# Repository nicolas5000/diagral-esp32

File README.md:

# diagral-uart-esp32
This project permits to connect to Diagral alarm system DIAG91AGFK using the 20 pins connector on the back (the connector used for the GSM board DIAG55AAX).

It permits to get status from and modify state of the alarm system as it could be done using call and SMS with official DIAG55AAX from Diagral, but using local MQTT connection... and it is directly recognized by Home Assistant!

This project is originally tested on XIAO-ESP32-S3 (with battery management by ESP32 board) and Waveshare ESP32-C6 (with battery management by the Diagral alarm system) hardware and based on ESP-IDF SDK version 6.0.2. It should also work with any other board compatible with Waveshare ESP32-S3 and ESP32-C6 board pinout.

This project is open source: you can reuse it and modify it, but please add a link to my project.
If you like this project you can [contribute](#how-to-contribute) or [buy me a coffee](https://buymeacoffee.com/nicolas5000) to support the tens of hours I spent on it :blush:.

### Why I did this project

From Diagral, DIAG55AAX (also known as DIAG55AAX1) is a 2G only mobile network board and DIAG55AAX5 is 2G/3G mobile network board. These boards will not work anymore in the future as the 2G and 3G mobile networks are being replaced by 4G and 5G networks. Of course you can buy the official Diagral 4G device to replace your old DIAG55AAX module.

The goal of this project is to connect your Diagral system locally to your Home Assistant without any Cloud based solution.

### **Disclaimer**  
> [!CAUTION]
> This tool is designed for educational and testing purposes, provided "as is", without warranty of any kind. It has no link with Diagral company. Creators and contributors are not responsible for any misuse or damage caused by this tool. Keep in mind that you should have a secure MQTT and Home Assistant instances to avoid any attack on your alarm system from your domotics.

### **Security**
To use this project in a secure way, you shall:
- Put the board on the back of the DIAG91AGFK so it is protected by your alarm system tamper mechanism.
- Put a password on command line access (at least in production, when not testing anymore).
- Use a secure network (Wifi password...).
- Use a secure MQTT connection (strong password, certificate...).
- Protect your Home Assistant access.
- If you want the best:
  - Sign your firmware and enable secure boot (see ESP-IDF documentation). This risk can be mitigated by using [HTTPS server for OTA update](#ota-over-https).
  - Enable flash encryption (see ESP-IDF documentation) to protect your Wifi password, command-line password and MQTT password. This risk is mitigated by putting the ESP32 on the back of the DIAG91AGFK (protected by your alarm system tamper mechanism).

### Documentation
This documentation contains useful information about the project, especially:
- [Hardware requirements](README.md#hardware-requirements) to use the project
- [Software configuration](doc/configuration.md) (hardware pins used, network and MQTT settings, ...)
- [Using command line](doc/command_line.md) to test and configure the project
- [MQTT topics and messages](doc/mqtt.md)
- [The project development](doc/development_guide.md) (structure of the project, how the source code is organized if you want to contribute or fork...)
- [The current knowledge about the protocol and commands](doc/protocol.md) used between DIAG91AGFK and DIAG55AAX

### Support
I try to give support on my free time. If you have questions you can open a subject and ask directly in English (for everyone to understand) or in French.

### Project status

These features are currently available:
- Get state from Diagral alarm system:
  - Mode (idle, setup, test)
  - Zones 1 to 4 status (disarmed, arming, armed, armed "home", triggered)
  - Battery charging state. Note: it works only if you have a battery connected to provide power to the device!
- Control the alarm system: Arm/"Arm home"/Disarm with or withour PIN code (choose before building firmware or from command line, can't be modified from MQTT and Home Assistant).
- Events:
  - Error event: event type (tamper, main power, battery, radio link, internet link, arm cancelled reason), harware type (system, sensor, command, siren), hardware number
  - Detection event: event type, sensor type, sensor number
  - Alert event: alert type (fire, alert, silent alert, duress disarm), command number
- Control the ESP32:
  - Reboot
  - Enable/disable logging
  - Enable/disable passive mode
- Connectivity:
  - Wifi (integrated to ESP32 chip) support
  - Ethernet support (based on W5500/WIZ850io module)
  - DHCP support, with DNS provided by DHCP server
  - Static IPv4 support, including manual DNS server configuration
- (S)NTP support for time synchronization (required to have valid timestamps in MQTT messages)
- Front-end:
  - Command line features: see [dedicated page](doc/command_line.md) for more information
    - Control the alarm system
    - Reboot ESP32
    - Change Wifi configuration without reflashing firmware (configuration applied after reboot)
    - Change DHCP/IPv4 configuration without reflashing firmware (configuration applied after reboot)
    - Change MQTT configuration without reflashing firmware (configuration applied after reboot)
    - Change Diagral configuration without reflashing firmware (configuration applied after reboot)
    - Note: command line features are password protected by default, change default password in project configuration before building firmware.
  - MQTT support: see [dedicated page](doc/mqtt.md) for more information
    - Discovery message is published and compatible with Home Assistant, permitting to automatically add device to it without extra configuration.
    - In addition:
      - A button is added to reboot the ESP32 board.
      - A switch is added to enable/disable Diagral layer logging (applied after reboot).
      - A switch is added to enable/disable Diagral passive mode (applied after reboot).
      - A text stores the firmware URL for OTA without starting an update.
      - An OTA Upgrade button starts the update, and an OTA Status sensor reports its outcome.
- Configuration storage to flash
- [OTA firmware update](#ota-update) (update from Wifi or Ethernet using an HTTP(S) server) with rollback.
- MQTT connectivity watchdog: if MQTT connection is broken more than 5 minutes, the ESP32 will notify the alarm system and reboot.

### Diagral DIAG91AGFK 20-pins connector
The DIAG91AGFK has a 20-pins connector on the back to connect the DIAG55AAX GSM module. We use this connector for our project. Please check pin numbers:

Here is the pin description for the connector:
| Pin # | Description | Used by the project? |
|----|---|---|
| 1 | Audio from DIAG91AGFK microphone, unknown format | No |
| 2 | Audio to DIAG91AGFK speaker, unknown format | No |
| 3 | Audio from DIAG91AGFK microphone, unknown format | No |
| 4 | Audio to DIAG91AGFK speaker, unknown format | No |
| 5 | GND | Yes (at least once) |
| 6 | GND | Yes (at least once) |
| 7 | Seems to be 2.8V (LVCMOS?) from DIAG91AGFK | No |
| 8 | RX for DIAG91AGFK / TX for DIAG55AAX and our project (0V at low state, 2.8V at high state) | Yes |
| 9 | "Signal" pin, low by default, set to 2.8V by DIAG91AGFK or DIAG55AAX a few ms before sending any command on corresponding TX (wake up?) | Yes |
| 10 | TX for DIAG91AGFK / RX for DIAG55AAX and our project (0V at low state, 2.8V at high state) | Yes |
| 11 | 3.3V from DIAG55AAX | No |
| 12 | Seems to be 2.8V (LVCMOS?) from DIAG91AGFK | No |
| 13 | GND | Yes (at least once) |
| 14 | GND | Yes (at least once) |
| 15 | GND | Yes (at least once) |
| 16 | Power from DIAG91AGFK | Yes (at least once) |
| 17 | +BATT from the project | Yes (at least once. If not using battery, use a 1N5819 to connect power from pin 16 or 18 to this pin) |
| 18 | Power from DIAG91AGFK | Yes (at least once) |
| 19 | +BATT from the project | Yes (at least once. If not using battery, use a 1N5819 to connect power from pin 16 or 18 to this pin) |
| 20 | +BATT from the project | Yes (at least once. If not using battery, use a 1N5819 to connect power from pin 16 or 18 to this pin) |

> [!NOTE]
> - It is not required to connect all GND pins as they are already connected together on DIAG91AGFK side. Connect your project board to at least 1 GND pin.
> - It is not required to connect all Power pins as they are already connected together on DIAG91AGFK side. Connect your project board to at least 1 power pin.
> - It is not required to connect all +BATT pins as they are already connected together on DIAG91AGFK side. Connect your project board to at least 1 +BATT pin.

### Hardware requirements

In order to use this project, you will need:
- ESP32 board:
  - For PCB "beta" and 1.0, use [Seeed Studio XIAO-ESP32-S3](https://www.amazon.fr/dp/B0BYSB66S5/).
  - For PCB 1.1, use Waveshare ESP32-C6 or ESP32-S3 (or from other provider, but with equivalent pinout).
- 5 or 6 resistors (see the schematics):
  - R1 and R2 are required only if you want to monitor battery voltage. You can choose any values but the voltage on the GPIO shall always remains under 3.3V! I chose to use the same resistors but it's not mandatory. You can modify min (0%) and max (100%) voltage values in the configuration.
  - R3 and R4 are always required as they permit to convert the voltage level between Diagral (2.8V) and ESP32 (3.3V) for "Signal" pin.
  - R5 and R6 are always required as they permit to convert the voltage level between Diagral (2.8V) and ESP32 (3.3V) for "ESP32 TX" pin. Please note that in my case R6 is not needed as the ESP32-S3 board from Seeed Studio and Waveshare already have a 499 ohm resistor internally.
- For PCB "beta" and 1.0, [XL74610](https://www.amazon.fr/dp/B0H2HY1DP9/) "ideal diode" if you plan to charge the battery from the DIAG91AGFK 5V power supply (in fact the DIAG91AGFK provides 4.5V and it is required to use at least 4.257V to fully charge a battery like 18650 that is 4.2V at 100%, so normal diode can't be used)
- 1 (PCB "beta" and 1.0) or 2 (PCB 1.1) 1N5819 diode(s).
- Wires:
  - To connect everything to the ESP32 board if you don't use a PCB.
  - To Replace R6 0 ohm resistor
  - On PCB "beta" and 1.0 only, to connect battery pins to XIAO back.
- USB cable to connect the ESP32 board to your computer for first flashing of the firmware.
- Battery (like 18650 battery, I didn't try to reuse the battery provided with the DIAG55AAX module but it could work) and its connector.
- [W5500](https://www.amazon.fr/dp/B0B775X737/) Ethernet module only if you don't want to use Wifi
- 20 pins connector to connect to DIAG91AGFK if you don't want to use "Dupont" wires on your final project board.

### PCB
I have created a [kicad](./kicad/) project for schematics and PCB routing. Current version of the PCB is 1.1.  
You can directly purchase a PCB (minimum order of 5 units) from PCBWay using this [link](https://www.pcbway.com/project/shareproject/diagral_esp32_gerber_d70e3251.html) or ask me for available PCB and passive components (I don't provide ESP32, W5500 and battery and I don't solder the components). 

> [!CAUTION]
> Please note that mounting the W5500 module to use the Ethernet link will require to cut the back of the DIAG91AGFK because the W5500 is too big as you can see:

#### PCB versions

| PCB # | ESP32 compatibility | Limitations |
|----|---|---|
| beta | [Seeed Studio XIAO-ESP32-S3](https://www.amazon.fr/dp/B0BYSB66S5/) | (1) (2) |
| 1.0 | [Seeed Studio XIAO-ESP32-S3](https://www.amazon.fr/dp/B0BYSB66S5/) | (2) |
| 1.1 | Waveshare [ESP32-C6-Zero](https://amzn.eu/d/0iYieorw) or [ESP32-S3-Zero](https://amzn.eu/d/05cgIHxE) (or equivalent pinout and footprint) | No known limitation |

Known limitations:
- (1) Ethernet module is not working on this PCB due to footprint error. Use this PCB only for Wifi project.
- (2) The 1N5819 is missing on this PCB. You have to cut the track between R1 and pin 19 of the connector and put the 1N5819 as shown on the schematics below (D2):

#### Available PCB from France

| PCB # | PCB price | Passive components (optional) | Quantity available |
|----|---|---|---|
| beta | 3€ | 2€ for 20-pin connector, 1x 1N5819, 1x XL74610, 3x 4.7k resistors, 1x 22k resistor, 1x 2.2k resistor | 3 (in stock) |
| 1.0 | 3€ | 2€ for 20-pin connector, 1x 1N5819, 1x XL74610, 3x 4.7k resistors, 1x 22k resistor, 1x 2.2k resistor | 4 (in stock) |
| 1.1 | 5€ | 1€ for 20-pin connector, 2x 1N5819, 3x 4.7k resistors, 1x 22k resistor, 1x 2.2k resistor | on demand |

Additional costs for packaging and shipping to France (bubble envelope with tracking number) : 4€

> [!NOTE]
> Not included: ESP32, W5500 Ethernet module, battery and its connector, soldering the components on the PCB.

Here is an example of components on PCB 1.0:

### Development environment

The development environment is based on:
- Visual Studio Code (also known as VSCode)
- ESP-IDF extension for VSCode and ESP-IDF SDK installed

### Starting guide

Here are a few steps to follow to start with this project:
1. If you are not familiar with VSCode and ESP-IDF, I encourage you to read ESP-IDF starting guide and try the "Hello world" example on your ESP32 board. You should be able to build the example, flash the binary to your ESP32 board and monitor the execution from ESP-IDF monitor tool before going to next step.
2. Download this project / clone the repository, then open the project folder in VSCode.
3. Solder the components on the PCB or use wires to connect all the pins on your prototyping board (see schematics above).
4. Copy and rename the sdkconfig.defaults_xxx file to sdkconfig.defaults depending on your hardware.
5. Choose the ESP32-S3 or ESP32-C6 target depending on your hardware.
6. Open "SDK Configuration Editor" to configure the project and go to "Diagral UART Project Configuration" section. Configure network and choose the GPIO pins you want to use to connect everything.
7. Provide your HTTPS public certificate for OTA (see [OTA section](#ota-update) to generate a certificate) or create an empty file named _ca_cert.pem_
8. Build the source code, flash it to the board and monitor (there is single button that does everything if you are confident, otherwise, use the 3 buttons in this order).

By default the project is configured with verbose enabled and not in passive mode: you can see what happens with detailed logs and you can control your Diagral alarm system. In active mode you can use the command line to send commands to your Diagral system. You can use passive mode to get frames from DIAG91AGFK to DIAG55AAX only (but you have to connect all 20 pins).

#### Passive mode

As previously explained, in passive mode (don't forget to enable verbose) you will get frames from DIAG91AGFK to DIAG55AAX only.
If you need to see all exchanges you will have to use another "spy UART project".

#### Active mode

In this mode you can control your alarm system.

> [!NOTE]
> Keep verbose enabled if you want to see what happens in Diagral UART layer. In addition to console, exchanged frames can be sent to a Syslog server.

### OTA update
In order to update the firmware from Wifi or Ethernet securely, you should use an HTTPS server. If you don't mind, you can also use a simple HTTP server. This section describes the 2 options.

Saving the URL no longer starts an update: it is stored in NVS and reused when the **OTA Upgrade** button is pressed. Clearing the URL disables the button. The download runs in a separate task so it does not block the MQTT event handler. See the [MQTT OTA workflow](doc/mqtt.md#ota-workflow) for URL requirements, command topics and status values.

Keep the update server restricted to your trusted local network. Do not expose it to the Internet.

> [!NOTE]
> After OTA is performed, the ESP32 will reboot automatically. Then, if MQTT is not able to connect within 60s, the rollback will be performed to reboot on previous firmware.

#### OTA over HTTPS
1. Generate your certificate and key: you can use the command `openssl req -x509 -newkey rsa:2048 -keyout ca_key.pem -out ca_cert.pem -days 365 -nodes`. Don't forget to use a CN field that matches the machine IP address or name (like _myserver.lan_) that will be used in the URL when performing OTA. Note: this file is required to build and be included within the first firmware to load using USB.
2. If needed, allow the update port only from your trusted LAN clients in the firewall. Do not expose the server to the Internet.
3. From the repository root, launch `python3 tools/simple_ota_https_server.py <BIN_DIR> <PORT> [CERT_DIR] --bind <LAN_IP>`. Use a certificate containing the same IP address or hostname used in the firmware URL, including its subject alternative name.
4. From Home Assistant, enter the URL of the .bin file: `https://myserver.lan:8070/diagral-uart-esp32.bin` assuming you are using port 8070 on machine myserver.lan
5. Press **OTA Upgrade** to start the update.
6. Wait for the ESP32 to reconnect and for **OTA Status** to report **Firmware validated** after the validation period.

The HTTPS helper requires Python 3.10 or newer and existing `ca_cert.pem` / `ca_key.pem` files. Keep the key outside the served directory and outside Git; the optional `CERT_DIR` selects their location and defaults to `BIN_DIR`. All relative paths are resolved from the current working directory. The helper never generates or overwrites certificates or keys.

The default bind address is `127.0.0.1`, so an explicit trusted LAN address is needed for ESP32 access. Only `diagral-uart-esp32.bin` is served by default, for GET and HEAD requests; directory listings and certificate/key paths are unavailable. Use `--file <FILENAME.bin>` to select another binary and `--allow-subnet <CIDR>` to restrict clients to your LAN subnet. Symlinks are not accepted as the selected firmware file. Stop the server with Ctrl+C after the update.

For example, with LAN address `192.168.1.18` and subnet `192.168.1.0/24`:

```sh
python3 tools/simple_ota_https_server.py build 8443 ../ota-certificates --bind 192.168.1.18 --allow-subnet 192.168.1.0/24
```

The helper tests run with `python3 -m unittest discover -s tools -p test_simple_ota_https_server.py -v`. HTTPS tests use a temporary certificate generated by OpenSSL; those tests are skipped if OpenSSL is unavailable, and the symlink test is skipped where creation is not permitted.

#### OTA over HTTP
1. Create an empty file named ca_cert.pem and disable option _Allow OTA update only over HTTPS_ in the project configuration before building the firmware
2. Open the update port in your firewall
3. Launch the HTTP server. You can use the command `python3 -m http.server 8070 --bind ::` in the build folder containing diagral-uart-esp32.bin
4. From Home Assistant, enter the URL of the .bin file: `http://myserver.lan:8070/diagral-uart-esp32.bin` assuming you are using port 8070 on machine myserver.lan
5. Press **OTA Upgrade** to start the update.
6. Wait for the ESP32 to reconnect and for **OTA Status** to report **Firmware validated** after the validation period.

### Home Assistant integration
The board will be automatically discovered by Home Assistant MQTT integration and provide controls (with control panel for all zones and for each zone), PIN code verification (if enabled in the configuration), events (detection, alert, error), diagnostics and OTA firmware update.

### How to contribute

You can mainly contribute to this project by:
- Testing this project on your DIAG91AGFK alarm system and reporting any issue.
- If you have development skills you can propose source code modification to fix issues.
- [Buy me a coffee](https://buymeacoffee.com/nicolas5000).

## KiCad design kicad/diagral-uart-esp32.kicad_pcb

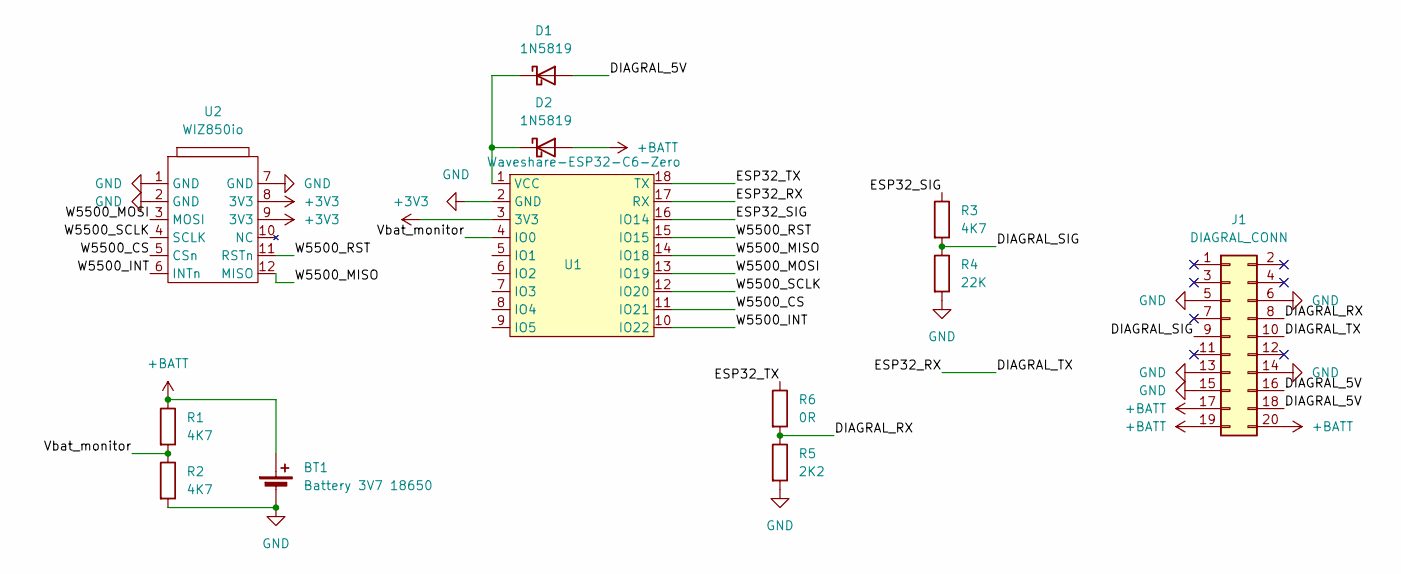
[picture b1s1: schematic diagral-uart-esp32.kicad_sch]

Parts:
BT1: Battery 3V7 18650; JST_XH_B2B-XH-A_1x02_P2.50mm_Vertical
D1, D2: 1N5819; D_DO-41_SOD81_P10.16mm_Horizontal
J1: DIAGRAL_CONN; PinHeader_2x10_P2.54mm_Vertical
R1, R2, R3: 4K7; R_Axial_DIN0207_L6.3mm_D2.5mm_P10.16mm_Horizontal
R4: 22K; R_Axial_DIN0207_L6.3mm_D2.5mm_P10.16mm_Horizontal
R5: 2K2; R_Axial_DIN0207_L6.3mm_D2.5mm_P10.16mm_Horizontal
R6: 0R; R_Axial_DIN0207_L6.3mm_D2.5mm_P10.16mm_Horizontal
U1: Waveshare-ESP32-C6-Zero
U2: WIZ850io

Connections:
+3V3: U1.3 (3V3), U2.8 (3V3), U2.9 (3V3)
+BATT: BT1.1 (+), D2.2 (A), J1.17, J1.19, J1.20, R1.1
/DIAGRAL_5V: D1.2 (A), J1.16, J1.18
/DIAGRAL_RX: J1.8, R5.1, R6.2
/DIAGRAL_SIG: J1.9, R3.2, R4.1
/DIAGRAL_TX: J1.10, U1.17 (RX)
/ESP32_SIG: R3.1, U1.16 (IO14)
/ESP32_TX: R6.1, U1.18 (TX)
/Vbat_monitor: R1.2, R2.1, U1.4 (IO0)
/W5500_CS: U1.11 (IO21), U2.5 (CSn)
/W5500_INT: U1.10 (IO22), U2.6 (INTn)
/W5500_MISO: U1.14 (IO18), U2.12 (MISO)
/W5500_MOSI: U1.13 (IO19), U2.3 (MOSI)
/W5500_RST: U1.15 (IO15), U2.11 (RSTn)
/W5500_SCLK: U1.12 (IO20), U2.4 (SCLK)
GND: BT1.2 (-), J1.5, J1.6, J1.13, J1.14, J1.15, R2.2, R4.2, R5.2, U1.2 (GND), U2.1 (GND), U2.2 (GND), U2.7 (GND)
unnamed: D1.1 (K), D2.1 (K), U1.1 (VCC)

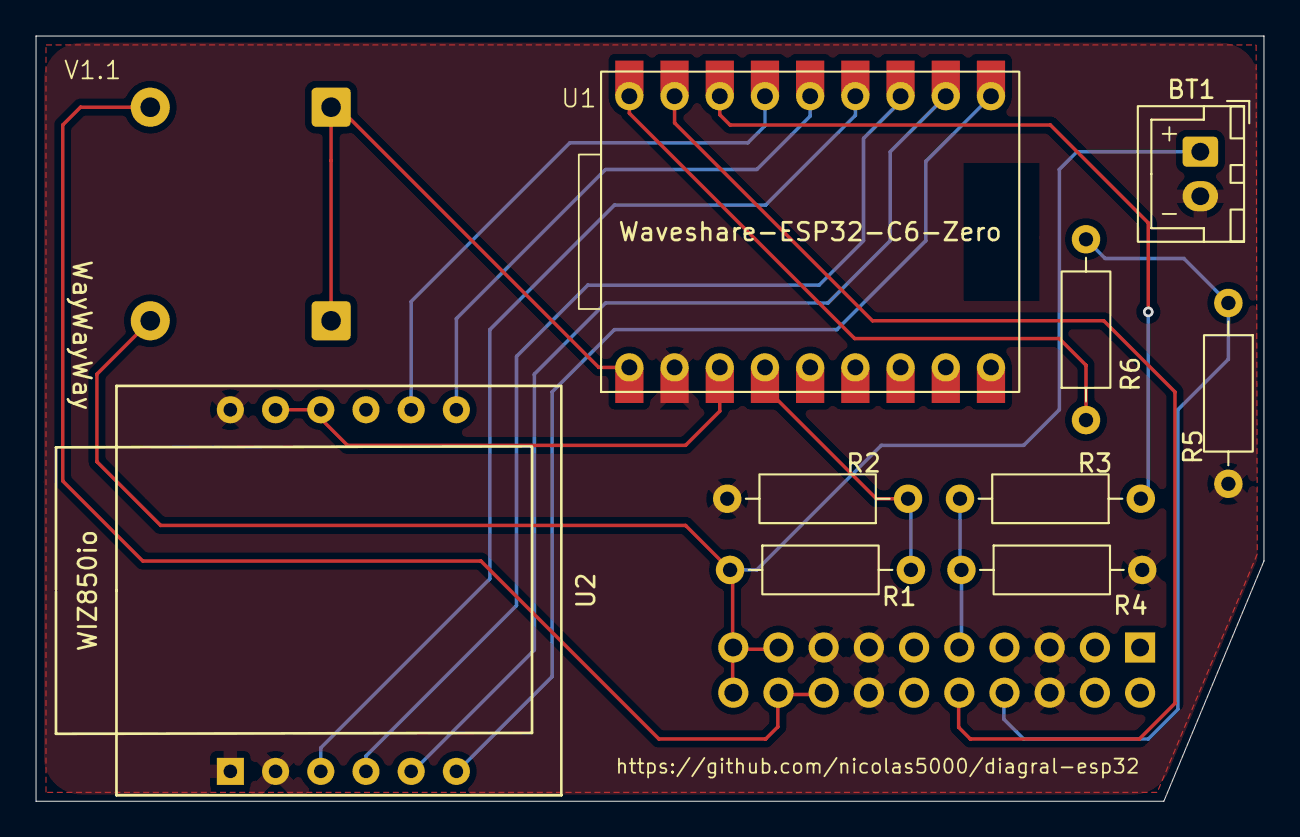
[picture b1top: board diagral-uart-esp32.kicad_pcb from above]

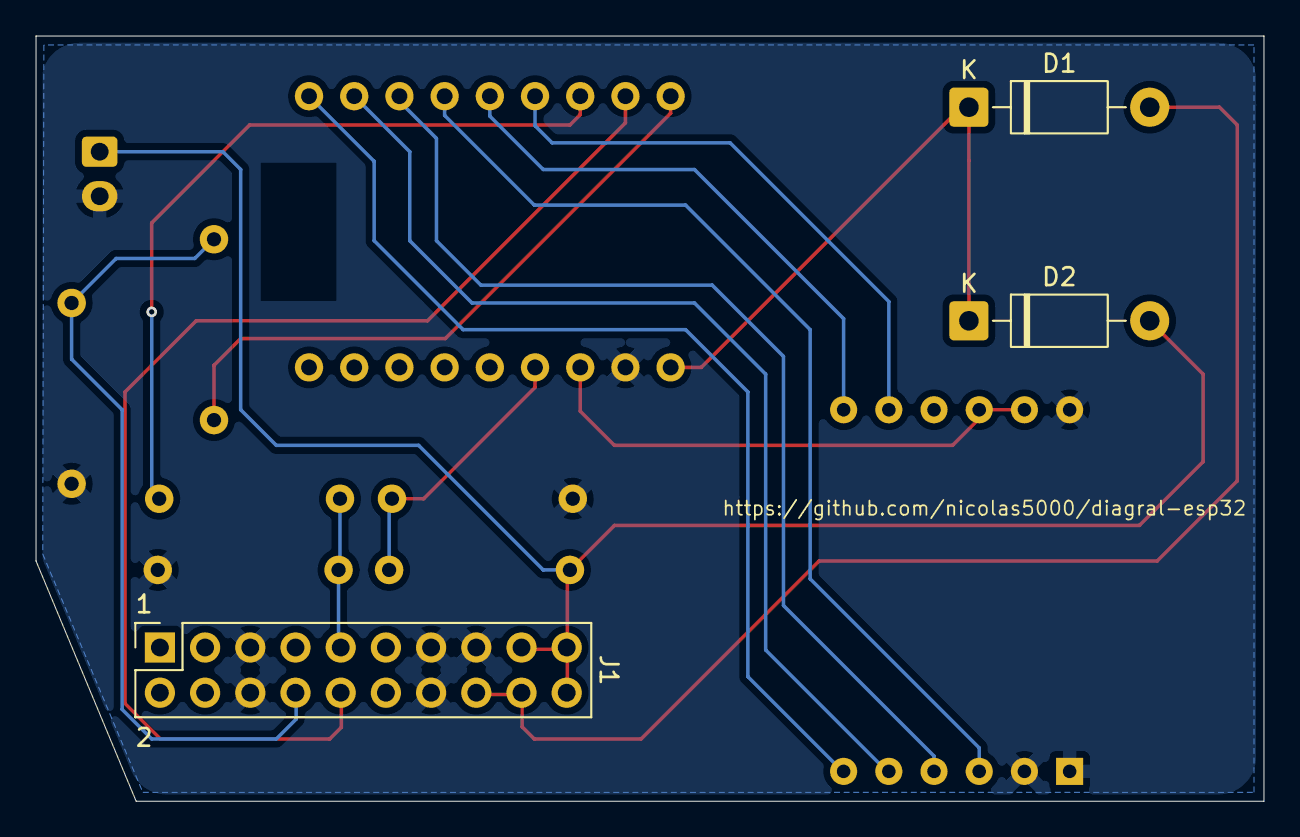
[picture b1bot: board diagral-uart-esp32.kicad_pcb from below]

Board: 2 copper layers, 69.0 x 43.0 mm, 12 parts (3 on the bottom side), 17 nets.
